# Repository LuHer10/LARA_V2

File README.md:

# LARA_V2

## Raspberry Pi Initial Configuration

### Step 1: Raspberry Pi OS

First flash the latest Raspberry Pi OS image to your preferred storage device.
The official Raspberry Pi Imager can be used for that.

Then perform an update
```bash
sudo apt update
```
### Step 2: Configure the CAN Hat for Steadywin motors

Add the following lines to /boot/firmware/config.txt
```bash
dtparam=spi=on
dtoverlay=mcp2515-can0,oscillator=8000000,interrupt=25,spimaxfrequency=1000000
```

Reboot
```bash
sudo reboot
```

See if initialization was successful
```bash
dmesg | grep -i '\(can\|spi\)'
```
It should output something like this:
```bash
[   20.892310] CAN device driver interface
[   20.915484] mcp251x spi0.0 can0: MCP2515 successfully initialized
```

Activate the CAN interface (example: 500000 baud)
```bash
sudo ip link set can0 up type can bitrate 500000
sudo ifconfig can0 txqueuelen 65536
sudo ifconfig can0 up
```

Optional: Activate CAN interface on boot

Add the following to ~/.bashrc
```bash
sudo ip link set can0 up type can bitrate 500000
sudo ifconfig can0 txqueuelen 65536
sudo ifconfig can0 up
```

### Step 3: Configure the serial port for the RoboClaw

### Step 4: Setup libraries for the Dynamixel servos

Download Dynamixel SDK
```bash
git clone https://github.com/ROBOTIS-GIT/DynamixelSDK.git
```

Install requirements
```bash
sudo apt-get install gcc
sudo apt-get install build-essential
```

Build the SDK
```bash
cd DynamixelSDK/c++/build/linux_sbc
sudo make install
```

Done!

## Steadywin GIM6010 Initial Configuration

### With ODriveTool

```python
odrv0.axis0.motor.config.current_lim = 3
odrv0.config.dc_bus_undervoltage_trip_level = 10

odrv0.axis0.config.can.heartbeat_rate_ms = 0
odrv0.axis0.config.can.encoder_rate_ms = 0

odrv0.save_configuration()
```

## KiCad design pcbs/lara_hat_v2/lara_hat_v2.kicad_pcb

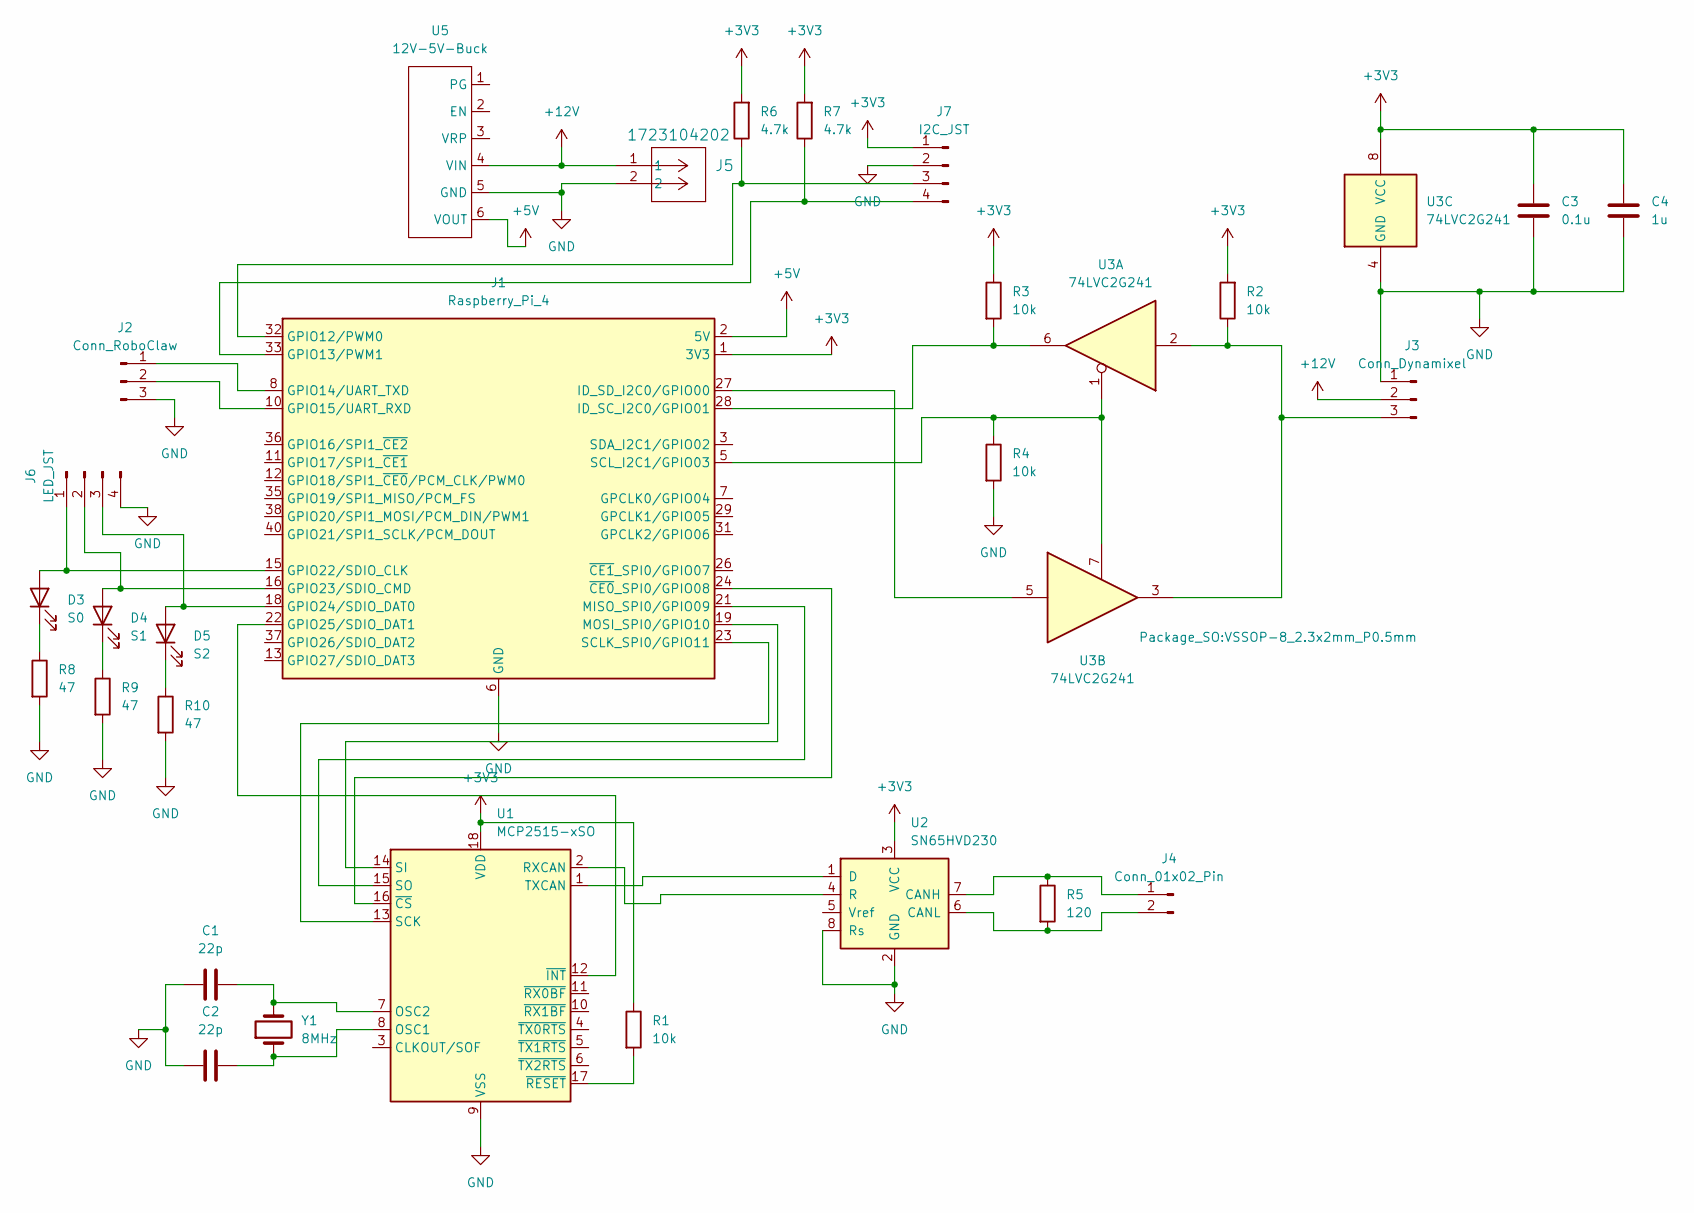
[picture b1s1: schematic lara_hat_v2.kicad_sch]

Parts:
C1, C2: 22p; C_0805_2012Metric_Pad1.18x1.45mm_HandSolder
C3: 0.1u; C_0805_2012Metric_Pad1.18x1.45mm_HandSolder
C4: 1u; C_0805_2012Metric_Pad1.18x1.45mm_HandSolder
D3: S0; LED_0805_2012Metric_Pad1.15x1.40mm_HandSolder
D4: S1; LED_0805_2012Metric_Pad1.15x1.40mm_HandSolder
D5: S2; LED_0805_2012Metric_Pad1.15x1.40mm_HandSolder
J1: Raspberry_Pi_4; PinHeader_2x20_P2.54mm_Vertical
J2: Conn_RoboClaw; JST_PH_B3B-PH-K_1x03_P2.00mm_Vertical
J3: Conn_Dynamixel; JST_EH_B3B-EH-A_1x03_P2.50mm_Vertical
J4: Conn_01x02_Pin; JST_PH_B2B-PH-K_1x02_P2.00mm_Vertical
J5: 1723104202; CONN_1723102000_02_MOL
J6: LED_JST; JST_PH_B4B-PH-K_1x04_P2.00mm_Vertical
J7: I2C_JST; JST_PH_B4B-PH-K_1x04_P2.00mm_Vertical
R1, R2, R3, R4: 10k; R_0805_2012Metric_Pad1.20x1.40mm_HandSolder
R5: 120; R_0805_2012Metric_Pad1.20x1.40mm_HandSolder
R6, R7: 4.7k; R_0805_2012Metric_Pad1.20x1.40mm_HandSolder
R8, R9, R10: 47; R_0805_2012Metric_Pad1.20x1.40mm_HandSolder
U1: MCP2515-xSO; SOIC-18W_7.5x11.6mm_P1.27mm
U2: SN65HVD230; SOIC-8_3.9x4.9mm_P1.27mm
U3: 74LVC2G241; VSSOP-8_2.3x2mm_P0.5mm
U5: 12V-5V-Buck; Pololu_Buck_12V_-_5V
Y1: 8MHz; Crystal_HC49-4H_Vertical

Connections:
+3V3: C3.1, C4.1, J1.1 (3V3), J1.17 (3V3), J7.1, R1.1, R2.2, R3.1, R6.2, R7.2, U1.18 (VDD), U2.3 (VCC), U3.8 (VCC)
+5V: J1.2 (5V), J1.4 (5V), U5.6 (VOUT)
+12V: J3.2, J5.1, U5.4 (VIN)
GND: C1.1, C2.1, C3.2, C4.2, J1.6 (GND), J1.9 (GND), J1.14 (GND), J1.20 (GND), J1.25 (GND), J1.30 (GND), J1.34 (GND), J1.39 (GND), J2.3, J3.1, J5.2, J6.4, J7.2, R4.2, R8.2, R9.2, R10.2, U1.9 (VSS), U2.2 (GND), U2.8 (Rs), U3.4 (GND), U5.5 (GND)
unnamed: D3.2 (A), J1.15 (GPIO22/SDIO_CLK), J6.1
unnamed: D3.1 (K), R8.1
unnamed: D4.2 (A), J1.16 (GPIO23/SDIO_CMD), J6.2
unnamed: D4.1 (K), R9.1
unnamed: D5.2 (A), J1.18 (GPIO24/SDIO_DAT0), J6.3
unnamed: D5.1 (K), R10.1
unnamed: J1.32 (GPIO12/PWM0), J7.3, R6.1
unnamed: J1.33 (GPIO13/PWM1), J7.4, R7.1
unnamed: J1.8 (GPIO14/UART_TXD), J2.1
unnamed: J1.10 (GPIO15/UART_RXD), J2.2
unnamed: J1.22 (GPIO25/SDIO_DAT1), U1.12 (~INT)
unnamed: J1.28 (ID_SC_I2C0/GPIO01), R3.2, U3.6
unnamed: J1.27 (ID_SD_I2C0/GPIO00), U3.5
unnamed: J1.21 (MISO_SPI0/GPIO09), U1.15 (SO)
unnamed: J1.19 (MOSI_SPI0/GPIO10), U1.14 (SI)
unnamed: J1.23 (SCLK_SPI0/GPIO11), U1.13 (SCK)
unnamed: J1.5 (SCL_I2C1/GPIO03), R4.1, U3.1, U3.7
unnamed: J1.24 (~CE0_SPI0/GPIO08), U1.16 (~CS)
unnamed: J3.3, R2.1, U3.2, U3.3
unnamed: J4.1, R5.1, U2.7 (CANH)
unnamed: J4.2, R5.2, U2.6 (CANL)
unnamed: C2.2, U1.8 (OSC1), Y1.1
unnamed: C1.2, U1.7 (OSC2), Y1.2
unnamed: U1.2 (RXCAN), U2.4 (R)
unnamed: U1.1 (TXCAN), U2.1 (D)
unnamed: R1.2, U1.17 (~RESET)

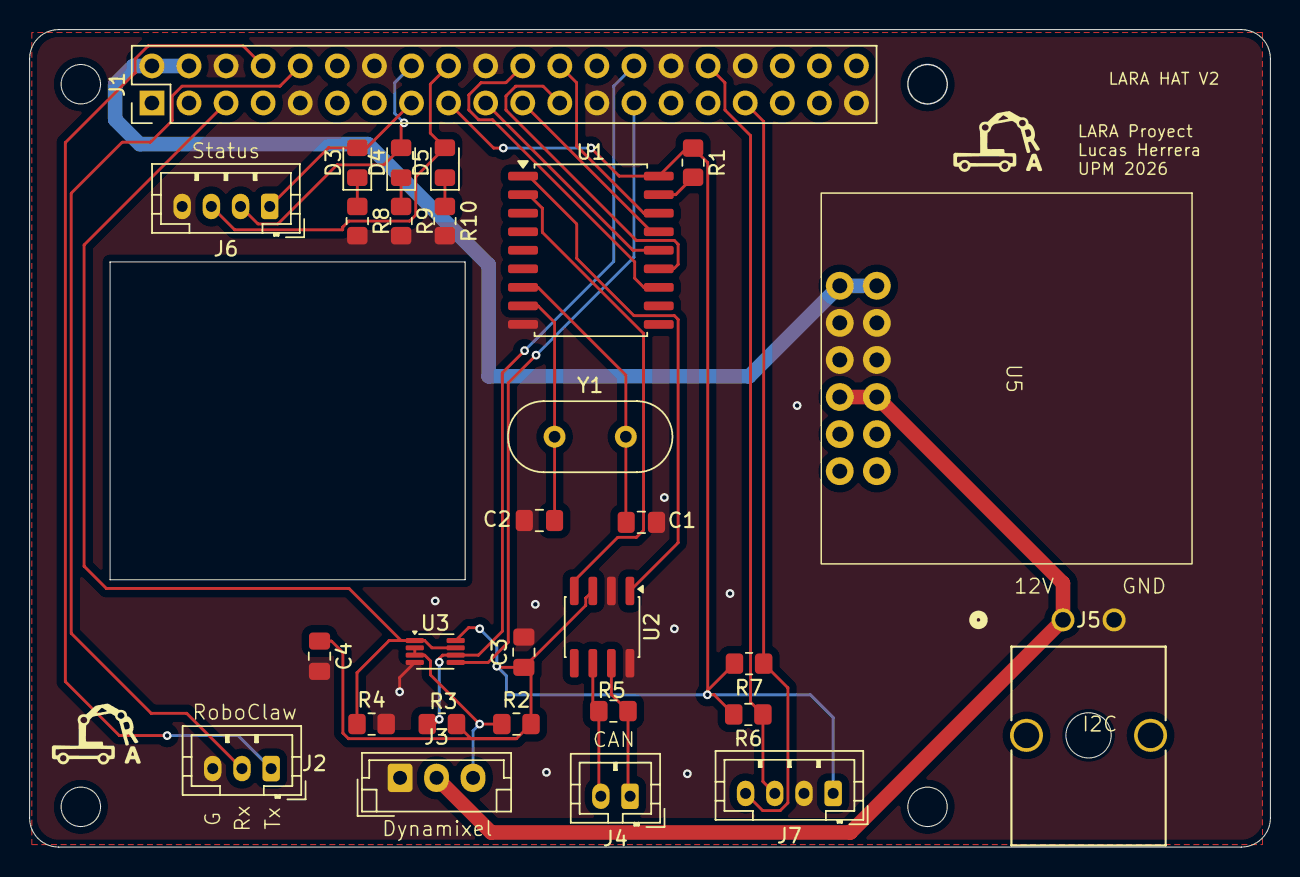
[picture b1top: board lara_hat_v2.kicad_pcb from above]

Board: 2 copper layers, 84.9 x 56.0 mm, 29 parts (0 on the bottom side), 30 nets.

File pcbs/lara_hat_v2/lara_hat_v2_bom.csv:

"Id";"Designator";"Footprint";"Quantity";"Designation";"Supplier and ref";
1;"C4";"C_0805_2012Metric_Pad1.18x1.45mm_HandSolder";1;"1u";;;
2;"D5";"LED_0805_2012Metric_Pad1.15x1.40mm_HandSolder";1;"S2";;;
3;"J5";"CONN_1723102000_02_MOL";1;"1723104202";;;
4;"J3";"JST_EH_B3B-EH-A_1x03_P2.50mm_Vertical";1;"Conn_Dynamixel";;;
5;"C2,C1";"C_0805_2012Metric_Pad1.18x1.45mm_HandSolder";2;"22p";;;
6;"J6";"JST_PH_B4B-PH-K_1x04_P2.00mm_Vertical";1;"LED_JST";;;
7;"U2";"SOIC-8_3.9x4.9mm_P1.27mm";1;"SN65HVD230";;;
8;"U5";"Pololu_Buck_12V_-_5V";1;"12V-5V-Buck";;;
9;"J1";"PinHeader_2x20_P2.54mm_Vertical";1;"Raspberry_Pi_4";;;
10;"J7";"JST_PH_B4B-PH-K_1x04_P2.00mm_Vertical";1;"I2C_JST";;;
11;"R5";"R_0805_2012Metric_Pad1.20x1.40mm_HandSolder";1;"120";;;
12;"J2";"JST_PH_B3B-PH-K_1x03_P2.00mm_Vertical";1;"Conn_RoboClaw";;;
13;"C3";"C_0805_2012Metric_Pad1.18x1.45mm_HandSolder";1;"0.1u";;;
14;"R2,R1,R3,R4";"R_0805_2012Metric_Pad1.20x1.40mm_HandSolder";4;"10k";;;
15;"Y1";"Crystal_HC49-4H_Vertical";1;"8MHz";;;
16;"R10,R9,R8";"R_0805_2012Metric_Pad1.20x1.40mm_HandSolder";3;"47";;;
17;"U3";"VSSOP-8_2.3x2mm_P0.5mm";1;"74LVC2G241";;;
18;"D3";"LED_0805_2012Metric_Pad1.15x1.40mm_HandSolder";1;"S0";;;
19;"U1";"SOIC-18W_7.5x11.6mm_P1.27mm";1;"MCP2515-xSO";;;
20;"R6,R7";"R_0805_2012Metric_Pad1.20x1.40mm_HandSolder";2;"4.7k";;;
21;"D4";"LED_0805_2012Metric_Pad1.15x1.40mm_HandSolder";1;"S1";;;
22;"J4";"JST_PH_B2B-PH-K_1x02_P2.00mm_Vertical";1;"Conn_01x02_Pin";;;

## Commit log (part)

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2026-05-05 added steadywin libraries and example
2026-05-12 added get_position function
2026-05-18 added missing Steadywin functions
2026-05-19 updated steadywin class
2026-05-19 new command line example
2026-05-26 added mutex for thread safety
2026-05-28 motor configuration updated
2026-06-11 big motor works now
2026-06-11 update README with additional steps for Raspberry Pi OS and CAN interface activation
2026-06-15 new mit test code
2026-06-16 added types.h file
2026-06-16 Updated Readme formotor configuration
2026-06-16 Updated GIM6010 library
2026-06-16 updated test examples
2026-06-30 new arm class
